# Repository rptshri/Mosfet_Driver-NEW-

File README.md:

# Mosfet_Driver-NEW-
this is the new mosfet driver using 2104 IC . Still needs to be tested. 

symbol for uC changed

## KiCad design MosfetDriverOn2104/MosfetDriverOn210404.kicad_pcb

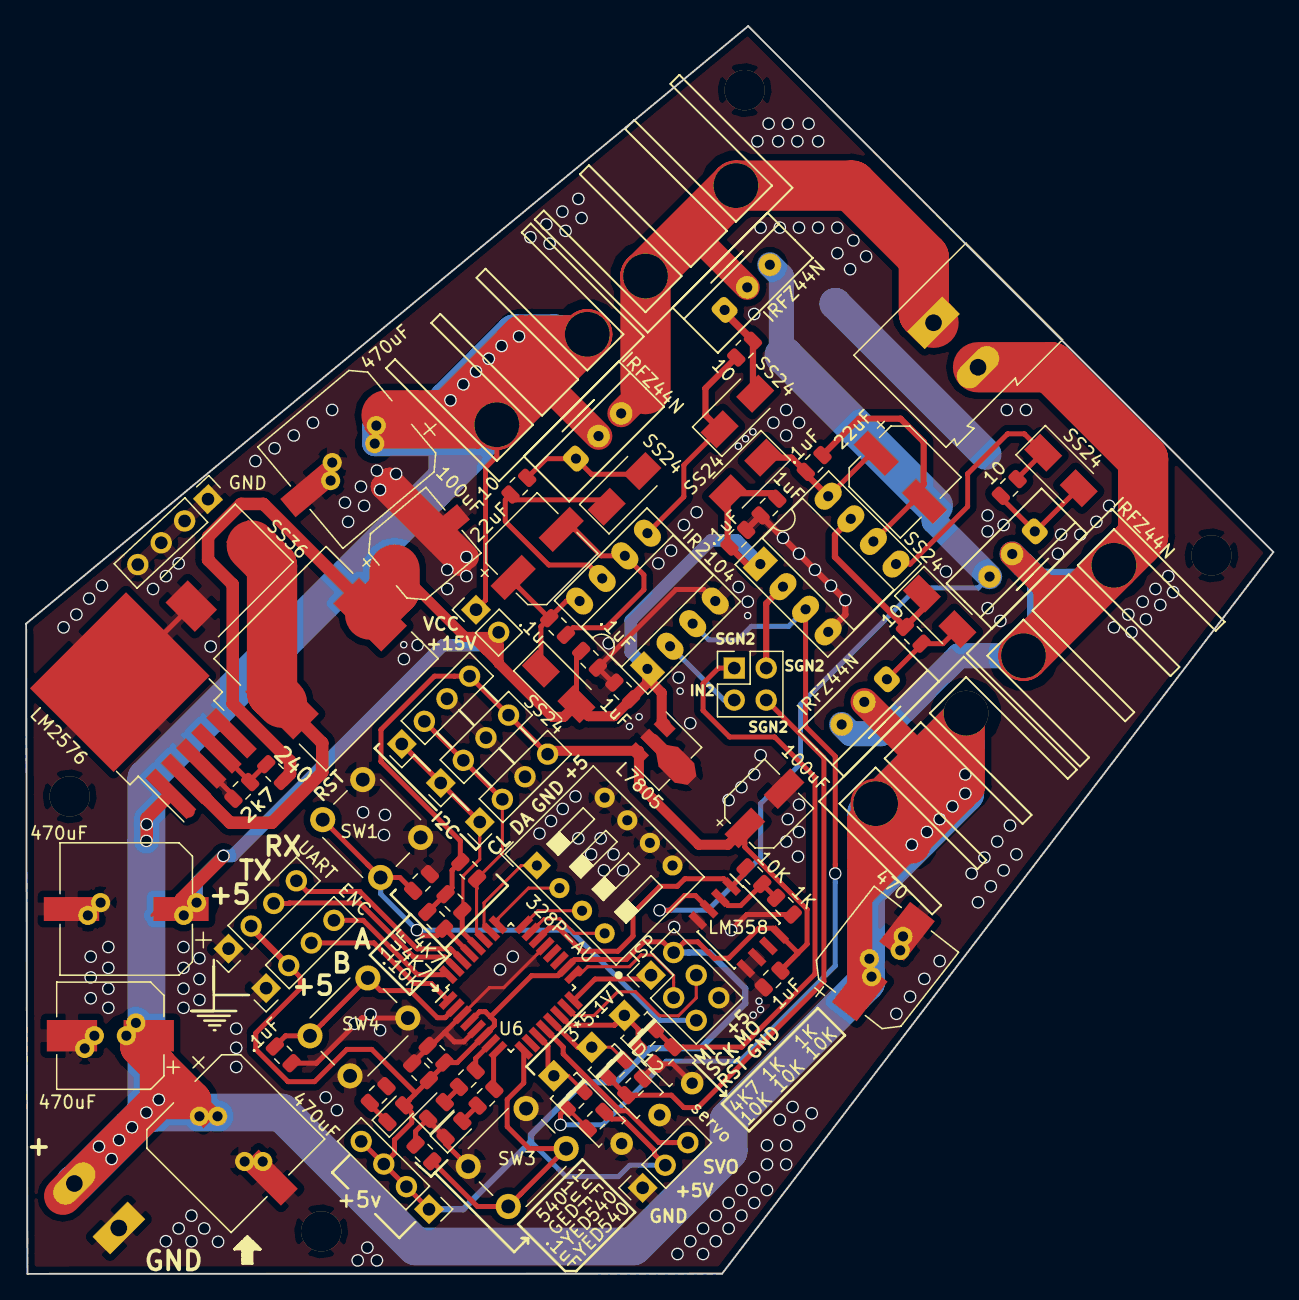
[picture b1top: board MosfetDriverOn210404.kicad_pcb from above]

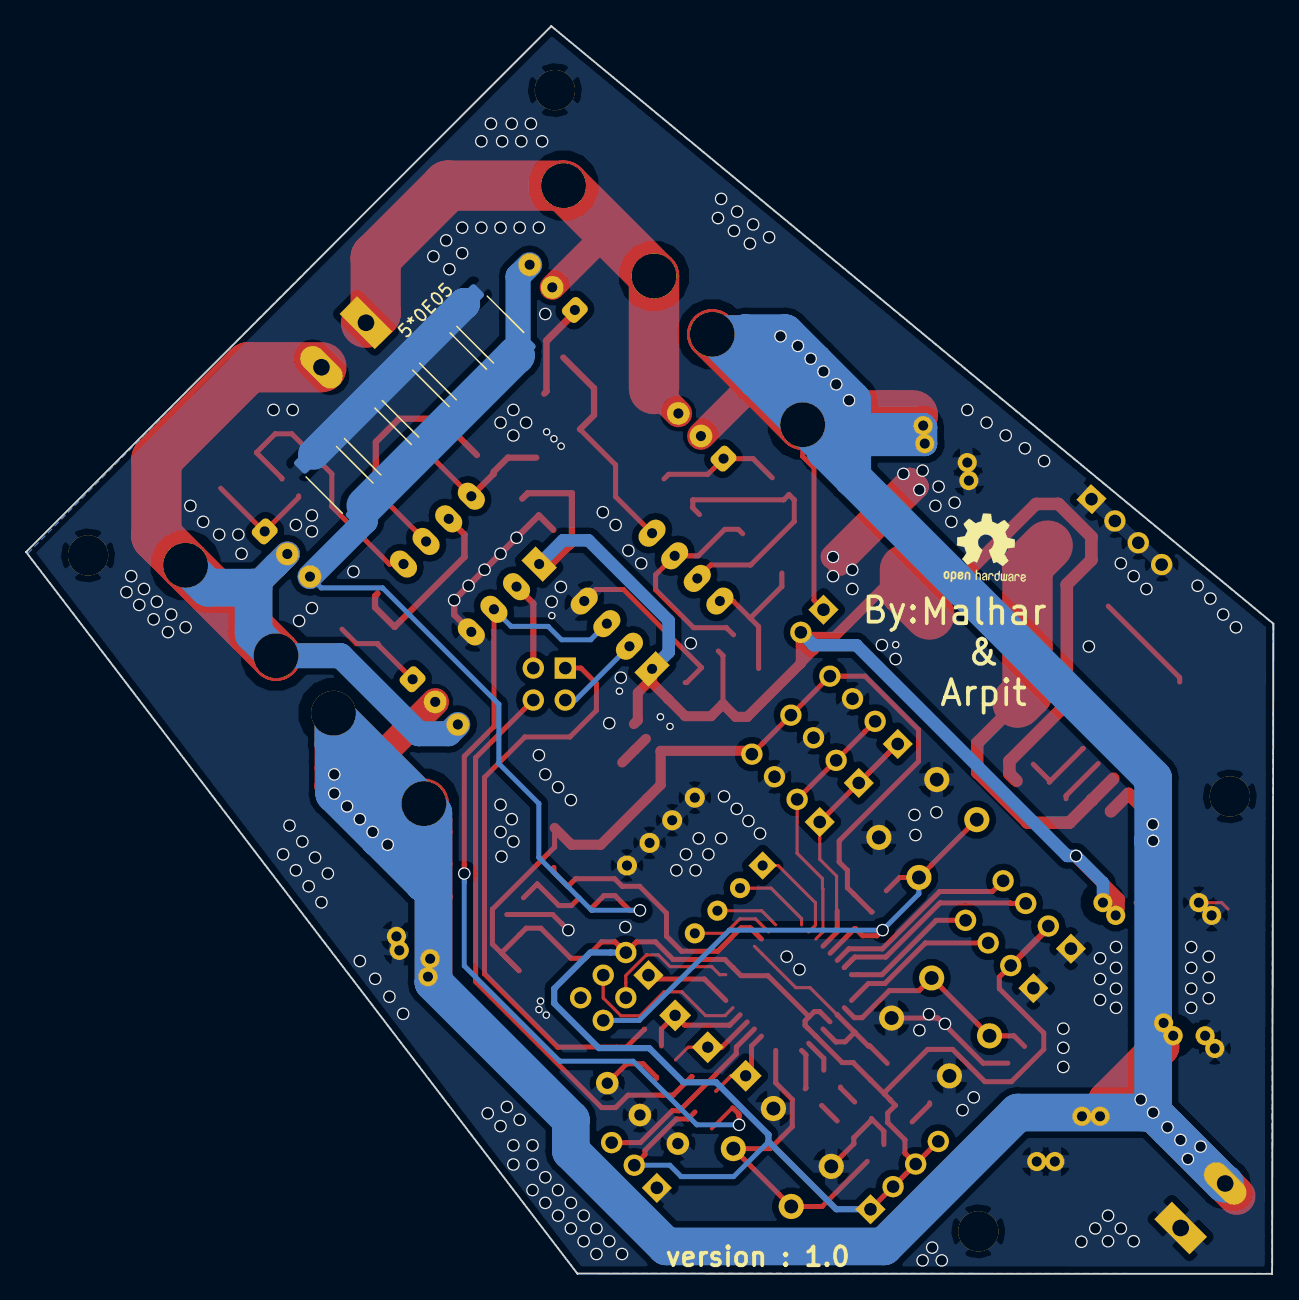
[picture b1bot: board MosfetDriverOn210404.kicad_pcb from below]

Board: 2 copper layers, 99.1 x 99.1 mm, 87 parts (5 on the bottom side), 53 nets.

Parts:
1K, 1K#2, 1K#3: 1K; R_0805_2012Metric
1uF, .1uF: C_Small; C_0805_2012Metric
1uF#2: C; C_0805_2012Metric
4K7: 4K7; R_0805_2012Metric
10, 10#2, 10#3, 10#4, 10K: R; R_0805_2012Metric
10K#2, 10K#3: 10K; R_0805_2012Metric
22uF, 22uF#2: 22u; CP_Elec_6.3x5.7
100uF: CP; CP_Elec_6.3x5.7
100uF#2: CP_Small; CP_Elec_5x4.4
470uF, 470uF#2: 470; CP_Elec_10x7.9
C1: 470uF; CP_Elec_8x6.2
C2: 470; CP_Elec_8x6.2
C10, C14: .1uF; C_0805_2012Metric
C12: 1uF; C_0805_2012Metric
C18: 470uF; CP_Elec_10x7.9
CB1, CB3, CB5: .1uF; C_0805_2012Metric
CB2, CB4: 1uF; C_0805_2012Metric
CB6: .1u; C_0805_2012Metric
D1: SS36; D_SMC
D2: GED; LED_0805_2012Metric
D3: SS24; D_SMA
D8: D; D_SMA
D10: LED; LED_0805_2012Metric
D11: 3*5.1V; D_A-405_P7.62mm_Horizontal
D12, D13: 5.1V; D_A-405_P7.62mm_Horizontal
IRFZ44N: IRF540N; TO220_HS_SCREW
ISP: AVR-ISP-6; PinHeader_2x03_P2.54mm_Vertical
J1, J3, J5: I2C HDR; PinHeader_1x04_P2.54mm_Vertical
J4: Screw_Terminal_01x02; TerminalBlock_Altech_AK300-2_P5.00mm
J6: UART; PinHeader_1x04_P2.54mm_Vertical
J7: 5V HDR; PinHeader_1x04_P2.54mm_Vertical
J8: GND; PinHeader_1x04_P2.54mm_Vertical
J9: servo; PinSocket_1x03_P2.54mm_Vertical
J10: ENC; PinHeader_1x04_P2.54mm_Vertical
J11: CROSS CONN; PinHeader_2x02_P2.54mm_Vertical
J12: motor; TerminalBlock_Altech_AK300-2_P5.00mm
J13: Conn_01x02_Female; PinHeader_1x02_P2.54mm_Vertical
L1: 220uH; L_12x12mm_H6mm
LM358: LM358; SOIC-8_3.9x4.9mm_P1.27mm
LM2576: LM2576HVS-ADJ; TO-263-5_TabPin3
Q2, Q3, Q4: IRFZ44N; TO220_HS_SCREW
R1: 240; R_0805_2012Metric
R2: 2k7; R_0805_2012Metric
R3, R17, R18: 540; R_0805_2012Metric
R7, R9, R11, R12: 0E05; R_2512_6332Metric
R8: 5*0E05; R_2512_6332Metric
R13, R19: 10K; R_0805_2012Metric
R20, R21: 4K7; R_0805_2012Metric
SS24, SS24#2, SS24#3, SS24#4: D; D_SMA
SW1, SW3, SW4: SW_Push; SW_PUSH_6mm
SW2: SW_DIP_x04; SW_DIP_SPSTx04_Slide_9.78x12.34mm_W7.62mm_P2.54mm
U2: L7805; SOT-89-3
U3, U5: IR2104; DIP-8_W7.62mm_Socket_LongPads
U6: 328P-AU; TQFP-32_7x7mm_P0.8mm
YED: YED; LED_0805_2012Metric

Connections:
+5V: 1uF.1, 1uF#2.1, 10K.2, 100uF#2.1, C12.1, D2.2, ISP.2, J1.4, J3.4, J5.4, J6.2, J7.1, J7.2, J7.3, J7.4, J9.2, J10.2, LM358.8, R19.1, R20.1, R21.1, U2.3, U6.4, U6.6, U6.18
+15V: 100uF.1, 470uF.1, CB2.1, CB3.1, CB4.1, CB5.1, D3.2, D8.2, J13.2, L1.2, R1.2, U2.1, U3.1, U5.1
/A: J10.4, U6.32
/B: J10.3, U6.1
/IN1: J11.2, U3.2
/IN2: J11.3, U5.2
/IS+: LM358.3, Q2.3, Q4.3, R7.1, R8.1, R9.1, R11.1, R12.1
/Isense: LM358.1, R13.2, U6.22
/M1: IRFZ44N.3, J12.2, Q2.2
/M2: J12.1, Q3.3, Q4.2
/MISO: ISP.1, U6.16
/MOSI: ISP.4, U6.15
/RST: C10.1, ISP.5, R19.2, SW1.2, U6.29
/RX: J6.4, U6.30
/SCK: ISP.3, U6.17
/SCL: J1.1, J3.1, J5.1, R20.2, U6.28
/SDA: J1.2, J3.2, J5.2, R21.2, U6.27
/SGN1: 1K#3.1, 10K#2.2, J11.4
/SGN2: 1K#2.1, 10K#3.2, J11.1
/TX: J6.3, U6.31
/svo: J9.3, U6.12
/~SD: 4K7.1, 10K.1, U3.3, U5.3
GND: 1K.2, 1uF.2, 1uF#2.2, 10K#2.1, 10K#3.1, 100uF.2, 100uF#2.2, 470uF.2, 470uF#2.2, .1uF.2, C1.2, C2.2, C10.2, C12.2, C14.2, C18.2, CB2.2, CB3.2, CB4.2, CB5.2, D1.2, D10.1, D11.2, D12.2, D13.2, ISP.6, J1.3, J3.3, J4.1, J5.3, J6.1, J8.1, J8.2, J8.3, J8.4, J9.1, J10.1, LM358.4, LM358.5, LM358.6, LM2576.3, LM2576.5, R2.2, R3.1, R7.2, R8.2, R9.2, R11.2, R12.2, SW1.1, SW2.5, SW2.6, SW2.7, SW2.8, SW3.2, SW4.2, U2.2, U3.4, U5.4, U6.3, U6.5, U6.21, YED.1
unnamed: 22uF#2.1, CB1.1, D3.1, U3.8
unnamed: 22uF#2.2, CB1.2, U3.6
unnamed: 22uF.1, CB6.1, D8.1, U5.8
unnamed: 22uF.2, CB6.2, U5.6
unnamed: C14.1, SW3.1, U6.9
unnamed: .1uF.1, SW4.1, U6.2
unnamed: D1.1, L1.1, LM2576.2
unnamed: D2.1, R3.2
unnamed: 10.2, SS24.1, U3.7
unnamed: 10.1, IRFZ44N.1, SS24.2
unnamed: 10#2.2, SS24#3.1, U3.5
unnamed: 10#2.1, Q2.1, SS24#3.2
unnamed: 10#3.2, SS24#2.1, U5.7
unnamed: 10#3.1, Q3.1, SS24#2.2
unnamed: 10#4.2, SS24#4.1, U5.5
unnamed: 10#4.1, Q4.1, SS24#4.2
unnamed: R17.2, YED.2
unnamed: D10.2, R18.2
unnamed: 4K7.2, D11.1, U6.11
unnamed: 1K#3.2, D12.1, U6.13
unnamed: 1K#2.2, D13.1, U6.14
unnamed: LM2576.4, R1.1, R2.1
unnamed: 1K.1, LM358.2, R13.1
unnamed: R17.1, U6.7
unnamed: R18.1, U6.8
unnamed: SW2.1, U6.26
unnamed: SW2.2, U6.25
unnamed: SW2.3, U6.24
unnamed: SW2.4, U6.23
VCC: 470uF#2.1, C1.1, C2.1, C18.1, IRFZ44N.2, J4.2, J13.1, LM2576.1, Q3.2

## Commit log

2018-10-20 Added .gitignore ,Fixes #1
2018-10-20 Started Creating New Sch
2018-10-20 folder for code added
2018-10-20 Create Mosfet_Driver_Code
2018-10-20 test upload
2018-10-20 symbol changed!
2018-10-20 schematic file updated
2018-10-21 #3 fixed
2018-10-21 #5 fixed, and many other changes.
2018-10-21 #4 fixed
2018-10-21 #4 ,switches footprints also changed to THT
2018-10-21 NEW footprint for MOSFET and Heatsink,fixes #6
    3D model is needed
2018-10-21 Schematcs updated with mosfet footprints
2018-10-21 bulk cap added
2018-10-21 starting with pcb, yet to place cpmparator
    i am not sure about the D2pack of 7805ic
2018-10-21 Started organising schematic
2018-10-21 Completed Hirarcheial Sch, fixes #9
2018-10-21 removed conflicts
2018-10-21 Revert "modified to merge"
    This reverts commit cf469160eef4a409041155a7ffafeab8deb317d8, reversing
    changes made to 7983ee0f074dadb39ee60eddebdc6a6efc4b26c3.
2018-10-21 Revert "Started organising schematic"
    This reverts commit bd680b048fb891cfeeabdb1f5b1f73ff93af24f7.
2018-10-22 fixes #4 , #3 ,
2018-10-22 started routing
2018-10-23 Sorted PCB
2018-10-23 Arrenged components,just need to pack a little bit tighter
2018-10-23 Started tightening board
2018-10-23 yet to arrange!
2018-10-23 comments
2018-10-23 necktie pattern
2018-10-23 add model for mosfet
2018-10-23 MOdified Footprint for TO220,REF https://github.com/botwot/kicad-lib/
2018-10-23 placement almost finalized !
2018-10-23 358 placed
2018-10-23 resistor footprint changed
2018-10-23 check
2018-10-24 longest diagonals for pcb: 89mm on y axis and 84mm on x axis
2018-10-24 Tested Route capability
2018-10-24 placements altered
2018-10-24 Applying different packing strategy
2018-10-24 we cant go compact in this layout, earlier was better
2018-10-25 Almost moved everything in
2018-10-25 Routing done...
2018-10-25 Completed Route
2018-11-03 #14 resolved
    vcc stiching done.
2018-11-04 #16 #15 #14 #12
2018-11-04 cap remaining
2018-11-05 cap smd with holes
2018-11-05 final commit for v1.0
